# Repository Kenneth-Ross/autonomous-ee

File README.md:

# Autonomous Control Board

Takes in edge commands and remote control; interprets into low level control systems. 
Interfaces a master ESP-32. 

- Throttle (Digital Potentiometer)
- Brakes   (Linear Actuator)
- Steering (Nema 34 Stepper Motor)

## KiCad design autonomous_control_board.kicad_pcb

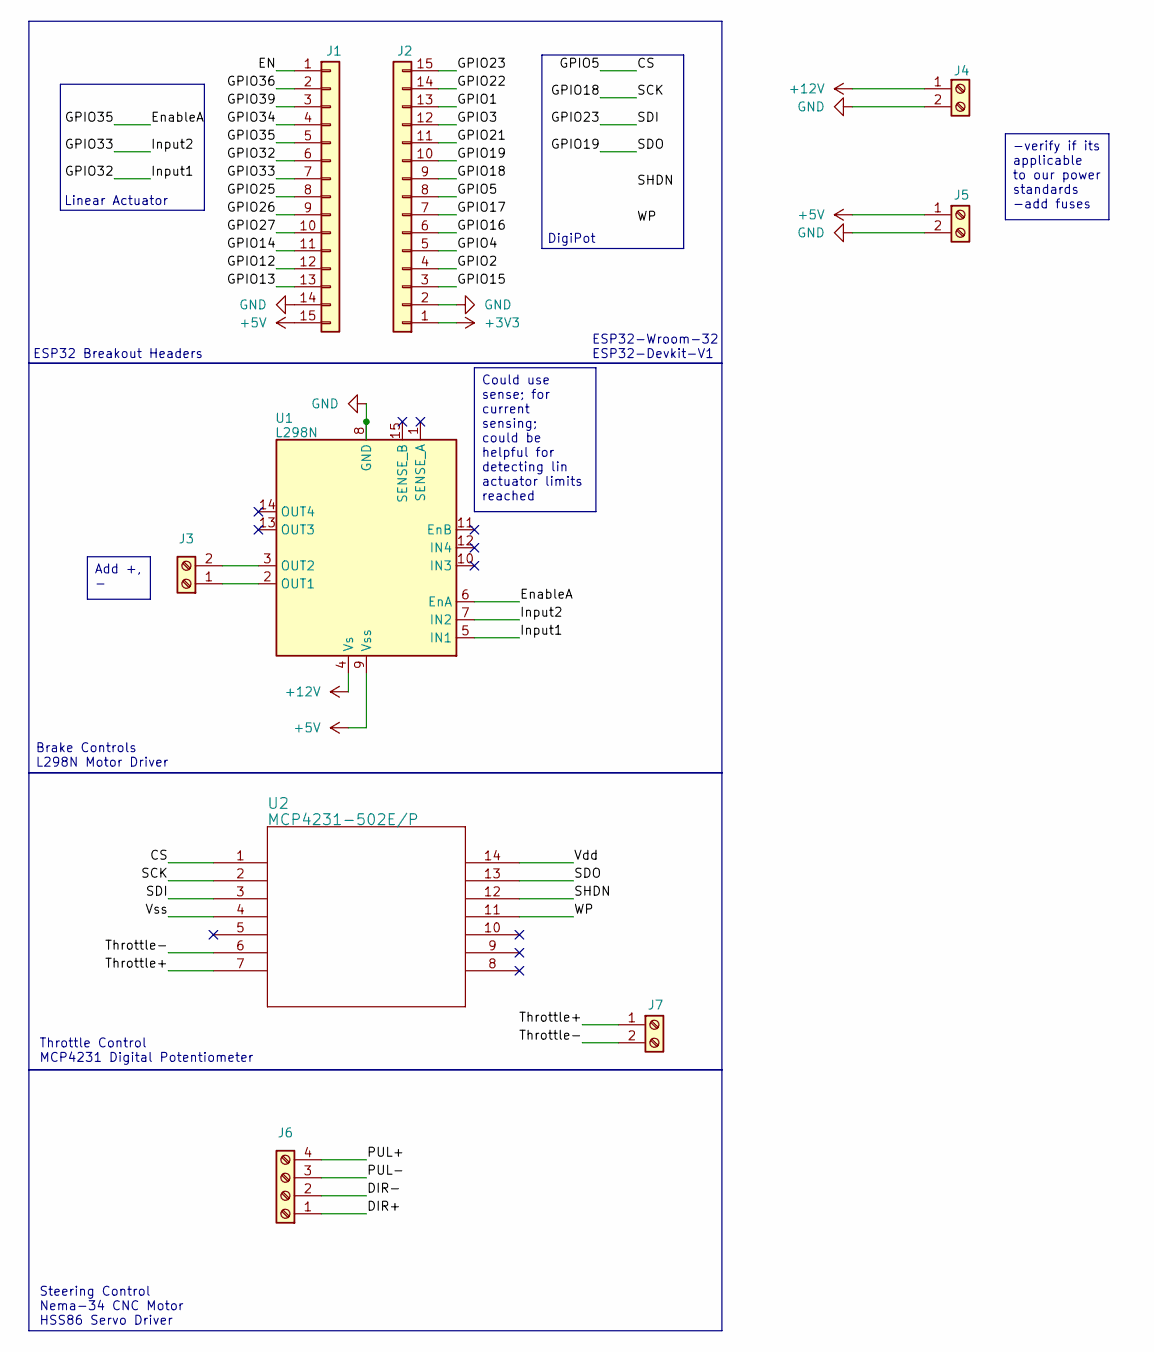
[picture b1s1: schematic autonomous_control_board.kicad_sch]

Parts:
J1, J2: Conn_01x15; PinSocket_1x15_P2.54mm_Vertical
J3, J4, J5, J7: Screw_Terminal_01x02; TerminalBlock_Phoenix_MPT-0,5-2-2.54_1x02_P2.54mm_Horizontal
J6: Screw_Terminal_01x04; TerminalBlock_Phoenix_MPT-0,5-4-2.54_1x04_P2.54mm_Horizontal
U1: L298N; TO-220-15_P2.54x5.08mm_StaggerOdd_Lead4.58mm_Vertical
U2: MCP4231-502E/P; DIP-14_W7.62mm

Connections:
+3V3: J2.1
+5V: J1.15, J5.1, U1.9 (Vss)
+12V: J4.1, U1.4 (Vs)
/CS: J2.8, U2.1
/DIR+: J6.1
/DIR-: J6.2
/EN: J1.1
/EnableA: J1.5, U1.6 (EnA)
/GPIO1: J2.13
/GPIO2: J2.4
/GPIO3: J2.12
/GPIO4: J2.5
/GPIO12: J1.12
/GPIO13: J1.13
/GPIO14: J1.11
/GPIO15: J2.3
/GPIO16: J2.6
/GPIO17: J2.7
/GPIO18: J2.9, U2.2
/GPIO19: J2.10, U2.13
/GPIO21: J2.11
/GPIO22: J2.14
/GPIO23: J2.15, U2.3
/GPIO25: J1.8
/GPIO26: J1.9
/GPIO27: J1.10
/GPIO32: J1.6, U1.5 (IN1)
/GPIO33: J1.7, U1.7 (IN2)
/GPIO34: J1.4
/GPIO36: J1.2
/GPIO39: J1.3
/PUL+: J6.4
/PUL-: J6.3
/SHDN: U2.12
/Throttle+: J7.1, U2.7
/Throttle-: J7.2, U2.6
/Vdd: U2.14
/Vss: U2.4
/WP: U2.11
GND: J1.14, J2.2, J4.2, J5.2, U1.8 (GND)
unnamed: J3.1, U1.2 (OUT1)
unnamed: J3.2, U1.3 (OUT2)

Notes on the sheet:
Throttle Control MCP4231 Digital Potentiometer
Brake Controls L298N Motor Driver
DigiPot
ESP32-Wroom-32 ESP32-Devkit-V1
Linear Actuator
Steering Control Nema-34 CNC Motor HSS86 Servo Driver
ESP32 Breakout Headers
-verify if its applicable to our power standards -add fuses
Could use sense; for current sensing; could be helpful for detecting lin actuator limits reached
Add +, -

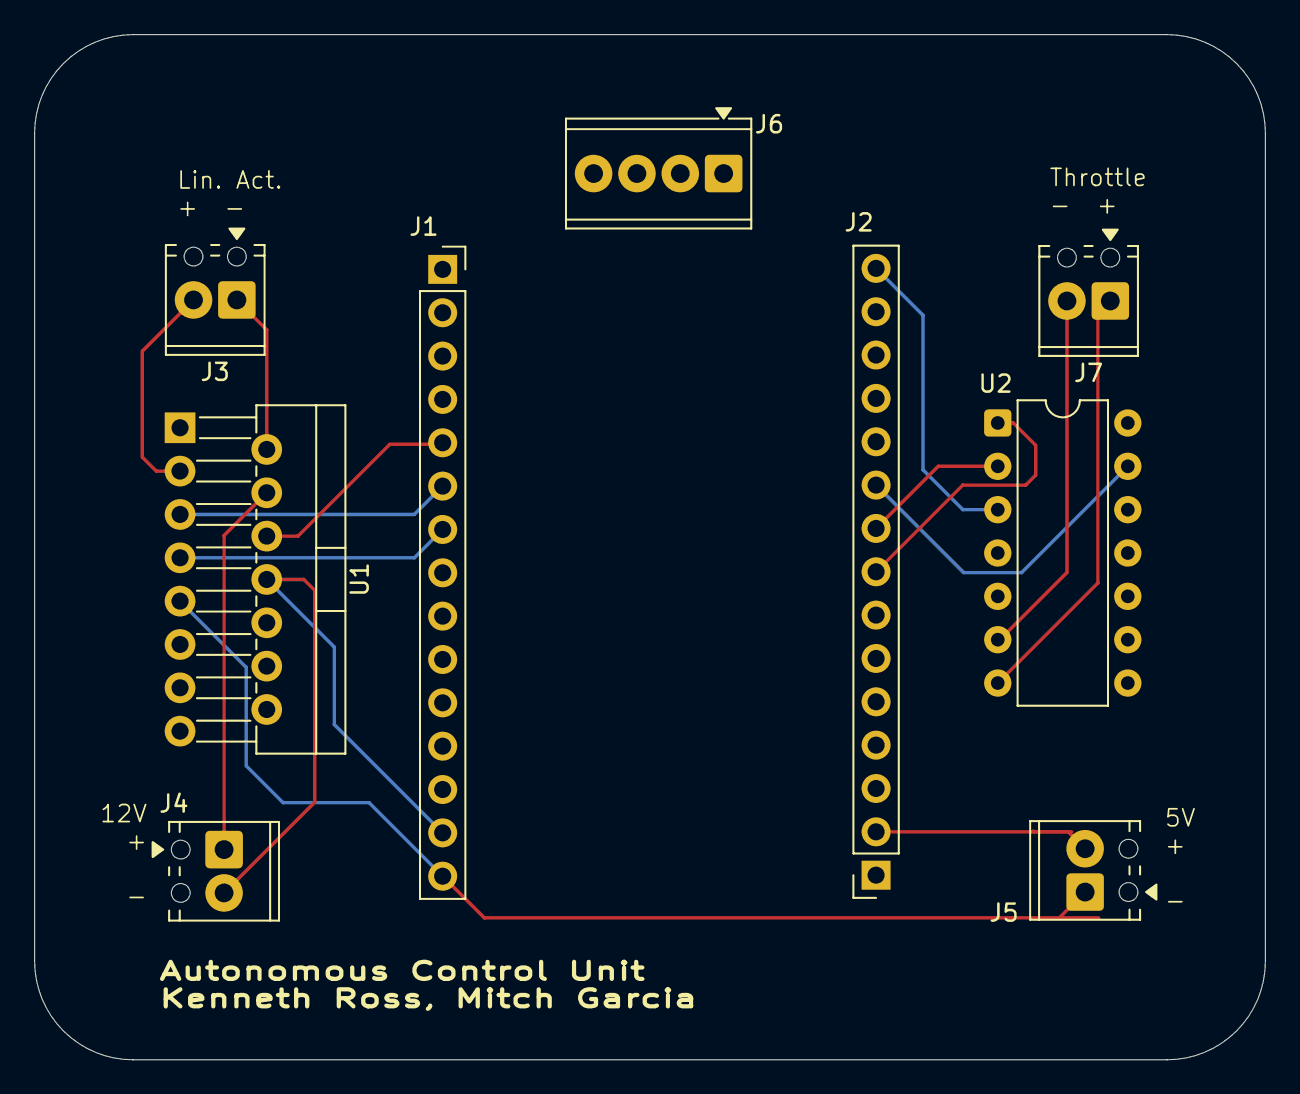
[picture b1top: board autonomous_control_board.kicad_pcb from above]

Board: 2 copper layers, 72.1 x 60.1 mm, 9 parts (0 on the bottom side), 14 nets.

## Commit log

2026-05-23 Added ESP32 Breakout, Brake Controls (L298N), Throttle Digipot (MCP4231)
2026-05-23 Added: Steering Control, Power Distribution (opting for commercial buck convertor)
2026-05-23 Started PCB design. Swapped out the right DigiPot
2026-05-23 Small changes
